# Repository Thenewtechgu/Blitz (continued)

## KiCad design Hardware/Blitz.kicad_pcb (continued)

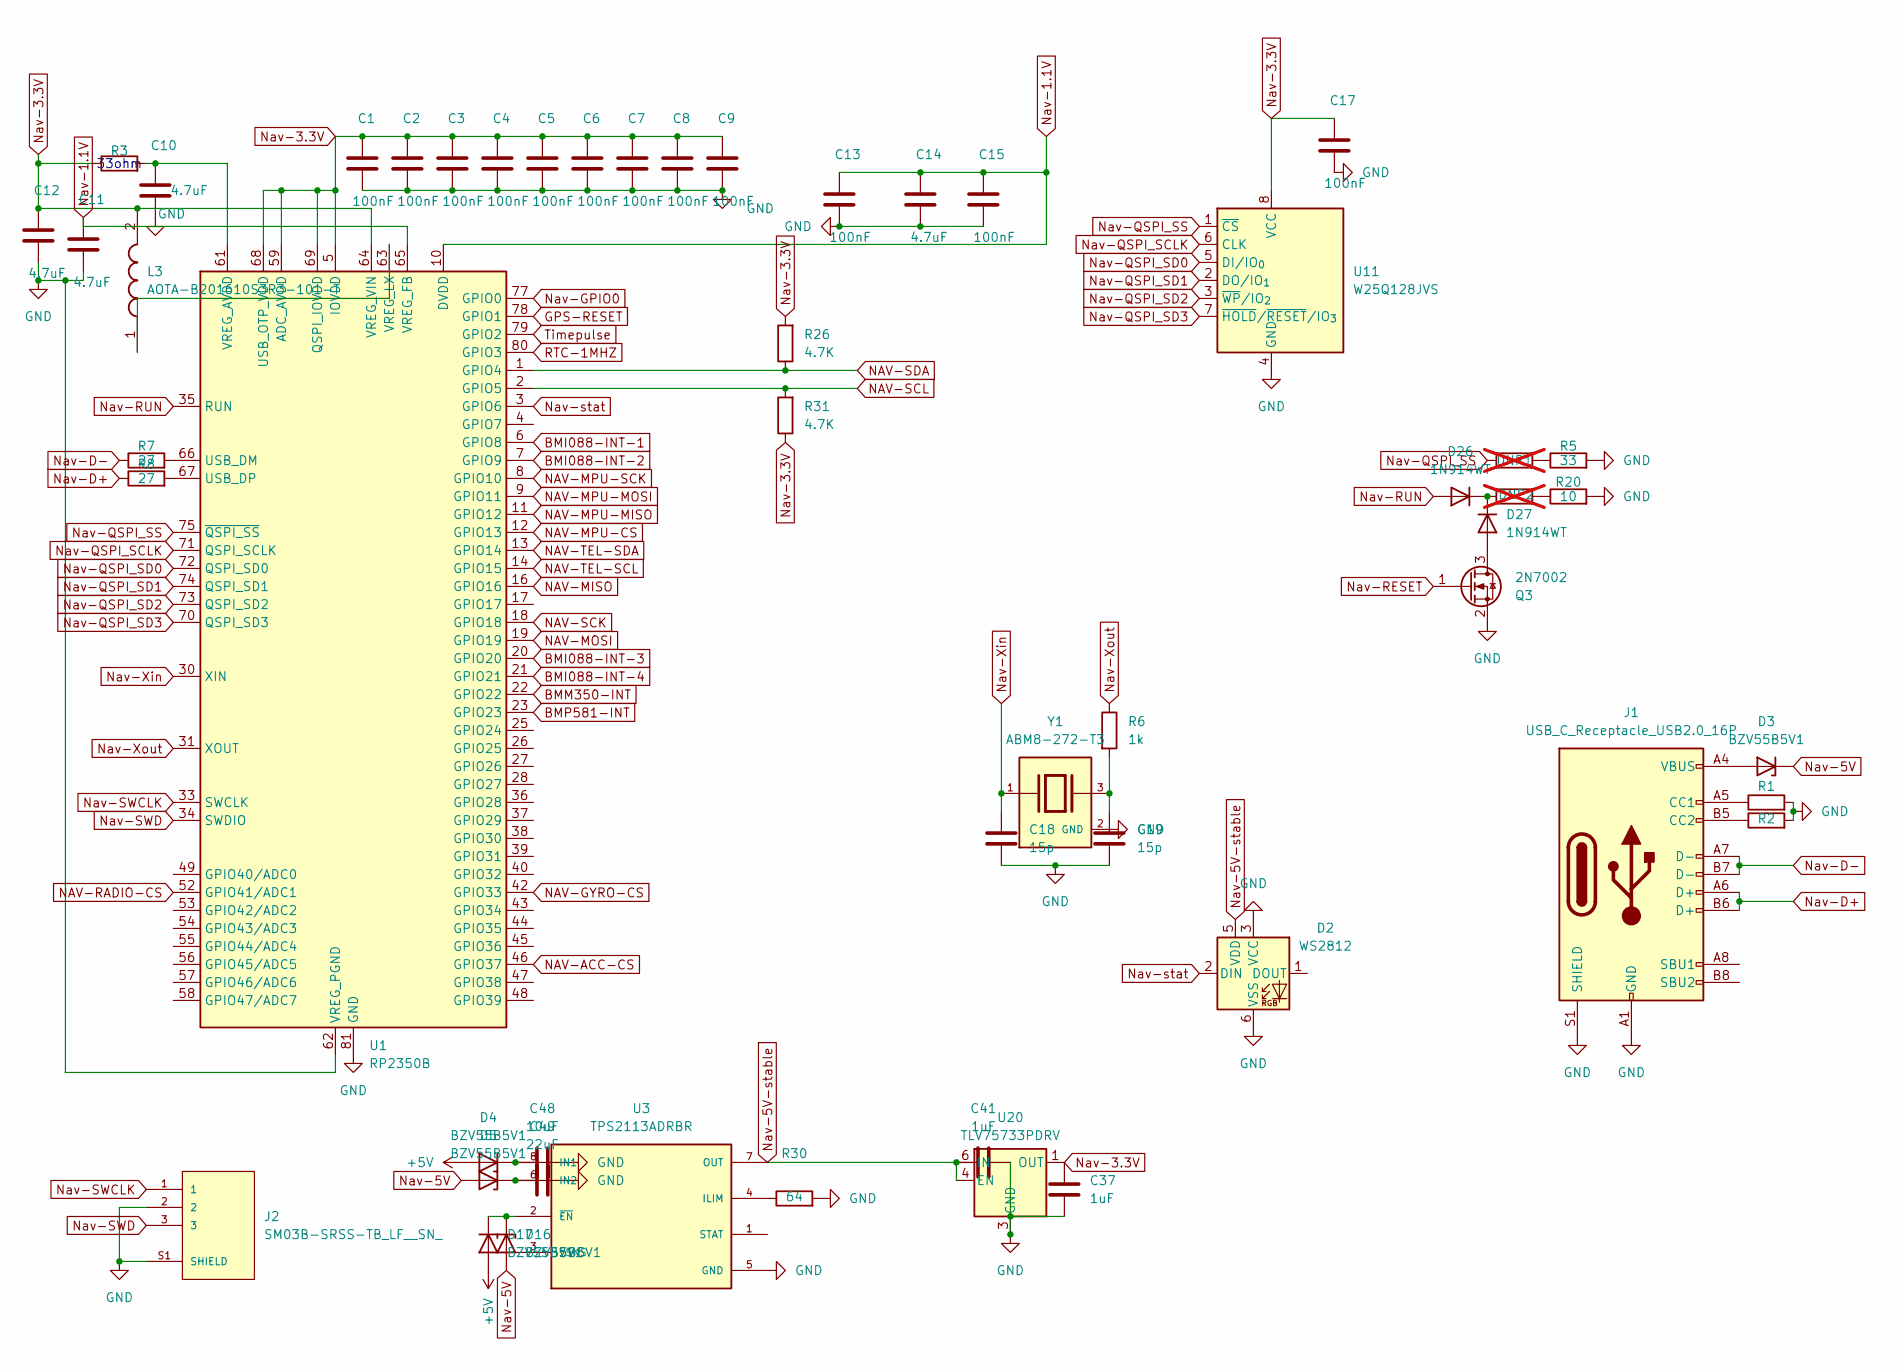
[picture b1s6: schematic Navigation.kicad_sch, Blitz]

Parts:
C1, C2, C3, C4, C5, C6, C7, C8, C9, C13, C15, C17: 100nF; C_01005_0402Metric
C10, C11, C12, C14: 4.7uF; C_01005_0402Metric
C18, C19: 15p; C_0201_0603Metric
C37, C41: 1uF; C_0402_1005Metric
C48: 10uF; C_1206_3216Metric_Pad1.33x1.80mm_HandSolder
C49: 22uF; C_1206_3216Metric_Pad1.33x1.80mm_HandSolder
D2: WS2812; LED_WS2812_PLCC6_5.0x5.0mm_P1.6mm
D3, D4, D5, D16, D17: BZV55B5V1; D_MiniMELF
D26, D27: 1N914WT; D_SOD-523
DNP1, DNP2: R; R_2010_5025Metric_Pad1.40x2.65mm_HandSolder; not fitted
J1: USB_C_Receptacle_USB2.0_16P; USB_C_Receptacle_G-Switch_GT-USB-7010ASV
J2: SM03B-SRSS-TB_LF__SN_; JST_SM03B-SRSS-TB_LF__SN_
L3: AOTA-B201610S3R3-101-T; AOTAB201610S3R3101T; Manufacturer_Part_Number AOTA-B201610S3R3-101-T; Mouser Part Number 815-AB201610S3R3101T
Q3: 2N7002; SOT-23
R1, R2: R; R_01005_0402Metric
R3: R; R_01005_0402Metric_Pad0.57x0.30mm_HandSolder
R5: 33; R_0201_0603Metric_Pad0.64x0.40mm_HandSolder
R6: 1k; R_01005_0402Metric
R7, R8: 27; R_0201_0603Metric_Pad0.64x0.40mm_HandSolder
R20: 10; R_0201_0603Metric_Pad0.64x0.40mm_HandSolder
R26, R31: 4.7K; R_0201_0603Metric
R30: 64; R_0201_0603Metric
U1: RP2350B; QFN-80-1EP_10x10mm_P0.4mm_EP3.4x3.4mm
U3: TPS2113ADRBR; SON65P300X300X100-9N; PARTREV C
U11: W25Q128JVS; SOIC-8_5.3x5.3mm_P1.27mm
U20: TLV75733PDRV; WSON-6-1EP_2x2mm_P0.65mm_EP1x1.6mm
Y1: ABM8-272-T3; XTAL_ABM8-272-T3; PARTREV 07-29-20

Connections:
+5V: D4.2 (A), D17.2 (A); also elsewhere on the board
BMI088-INT-1: U1.6 (GPIO8); also elsewhere on the board
BMI088-INT-2: U1.7 (GPIO9); also elsewhere on the board
BMI088-INT-3: U1.20 (GPIO20); also elsewhere on the board
BMI088-INT-4: U1.21 (GPIO21); also elsewhere on the board
BMM350-INT: U1.22 (GPIO22); also elsewhere on the board
BMP581-INT: U1.23 (GPIO23); also elsewhere on the board
GPS-RESET: U1.78 (GPIO1); also elsewhere on the board
NAV-ACC-CS: U1.46 (GPIO37); also elsewhere on the board
NAV-GYRO-CS: U1.42 (GPIO33); also elsewhere on the board
NAV-MISO: U1.16 (GPIO16); also elsewhere on the board
NAV-MOSI: U1.19 (GPIO19); also elsewhere on the board
NAV-MPU-CS: U1.12 (GPIO13); also elsewhere on the board
NAV-MPU-MISO: U1.11 (GPIO12); also elsewhere on the board
NAV-MPU-MOSI: U1.9 (GPIO11); also elsewhere on the board
NAV-MPU-SCK: U1.8 (GPIO10); also elsewhere on the board
NAV-RADIO-CS: U1.52 (GPIO41/ADC1)
NAV-SCK: U1.18 (GPIO18); also elsewhere on the board
NAV-SCL: R31.2, U1.2 (GPIO5)
NAV-SDA: R26.1, U1.1 (GPIO4)
NAV-TEL-SCL: U1.14 (GPIO15); also elsewhere on the board
NAV-TEL-SDA: U1.13 (GPIO14); also elsewhere on the board
Nav-1.1V: C11.1, C13.1, C14.1, C15.1, U1.10 (DVDD), U1.32 (DVDD), U1.51 (DVDD), U1.65 (VREG_FB)
Nav-3.3V: C1.1, C2.1, C3.1, C4.1, C5.1, C6.1, C7.1, C8.1, C9.1, C12.1, C17.1, C37.1, L3.2, R3.1, R26.2, R31.1, U1.5 (IOVDD), U1.15 (IOVDD), U1.24 (IOVDD), U1.29 (IOVDD), U1.41 (IOVDD), U1.50 (IOVDD), U1.59 (ADC_AVDD), U1.60 (IOVDD), U1.64 (VREG_VIN), U1.68 (USB_OTP_VDD), U1.69 (QSPI_IOVDD), U1.76 (IOVDD), U11.8 (VCC), U20.1 (OUT); also elsewhere on the board
Nav-5V: D3.1 (K), D5.2 (A), D16.2 (A)
Nav-5V-stable: C41.1, D2.5 (VDD), U3.7 (OUT), U20.4 (EN), U20.6 (IN)
Nav-D+: J1.A6 (D+), J1.B6 (D+), R8.1
Nav-D-: J1.A7 (D-), J1.B7 (D-), R7.1
Nav-GPIO0: U1.77 (GPIO0)
Nav-QSPI_SCLK: U1.71 (QSPI_SCLK), U11.6 (CLK)
Nav-QSPI_SD0: U1.72 (QSPI_SD0), U11.5 (DI/IO_{0})
Nav-QSPI_SD1: U1.74 (QSPI_SD1), U11.2 (DO/IO_{1})
Nav-QSPI_SD2: U1.73 (QSPI_SD2), U11.3 (~WP/IO_{2})
Nav-QSPI_SD3: U1.70 (QSPI_SD3), U11.7 (~HOLD/~RESET/IO_{3})
Nav-QSPI_SS: DNP1.1, U1.75 (~QSPI_SS), U11.1 (~CS)
Nav-RESET: Q3.1 (G)
Nav-RUN: D26.2 (A), U1.35 (RUN)
Nav-SWCLK: J2.1, U1.33 (SWCLK)
Nav-SWD: J2.3, U1.34 (SWDIO)
Nav-Xin: C18.1, U1.30 (XIN), Y1.1
Nav-Xout: R6.1, U1.31 (XOUT)
Nav-stat: D2.2 (DIN), U1.3 (GPIO6)
unnamed: C19.1, R6.2, Y1.3
unnamed: D3.2 (A), J1.A4 (VBUS), J1.A9 (VBUS), J1.B4 (VBUS), J1.B9 (VBUS)
unnamed: C48.1, D4.1 (K), U3.8 (IN1)
unnamed: C49.1, D5.1 (K), U3.6 (IN2)
unnamed: D16.1 (K), D17.1 (K), U3.2 (~EN)
unnamed: D26.1 (K), D27.1 (K), DNP2.1
unnamed: D27.2 (A), Q3.3 (D)
unnamed: DNP1.2, R5.1
unnamed: DNP2.2, R20.1
unnamed: J1.A5 (CC1), R1.1
unnamed: J1.B5 (CC2), R2.1
unnamed: R7.2, U1.66 (USB_DM)
unnamed: R8.2, U1.67 (USB_DP)
unnamed: C10.1, R3.2, U1.61 (VREG_AVDD)
unnamed: L3.1, U1.63 (VREG_LX)
unnamed: R30.1, U3.4 (ILIM)
RTC-1MHZ: U1.80 (GPIO3); also elsewhere on the board
Timepulse: U1.79 (GPIO2); also elsewhere on the board

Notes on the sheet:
33ohm

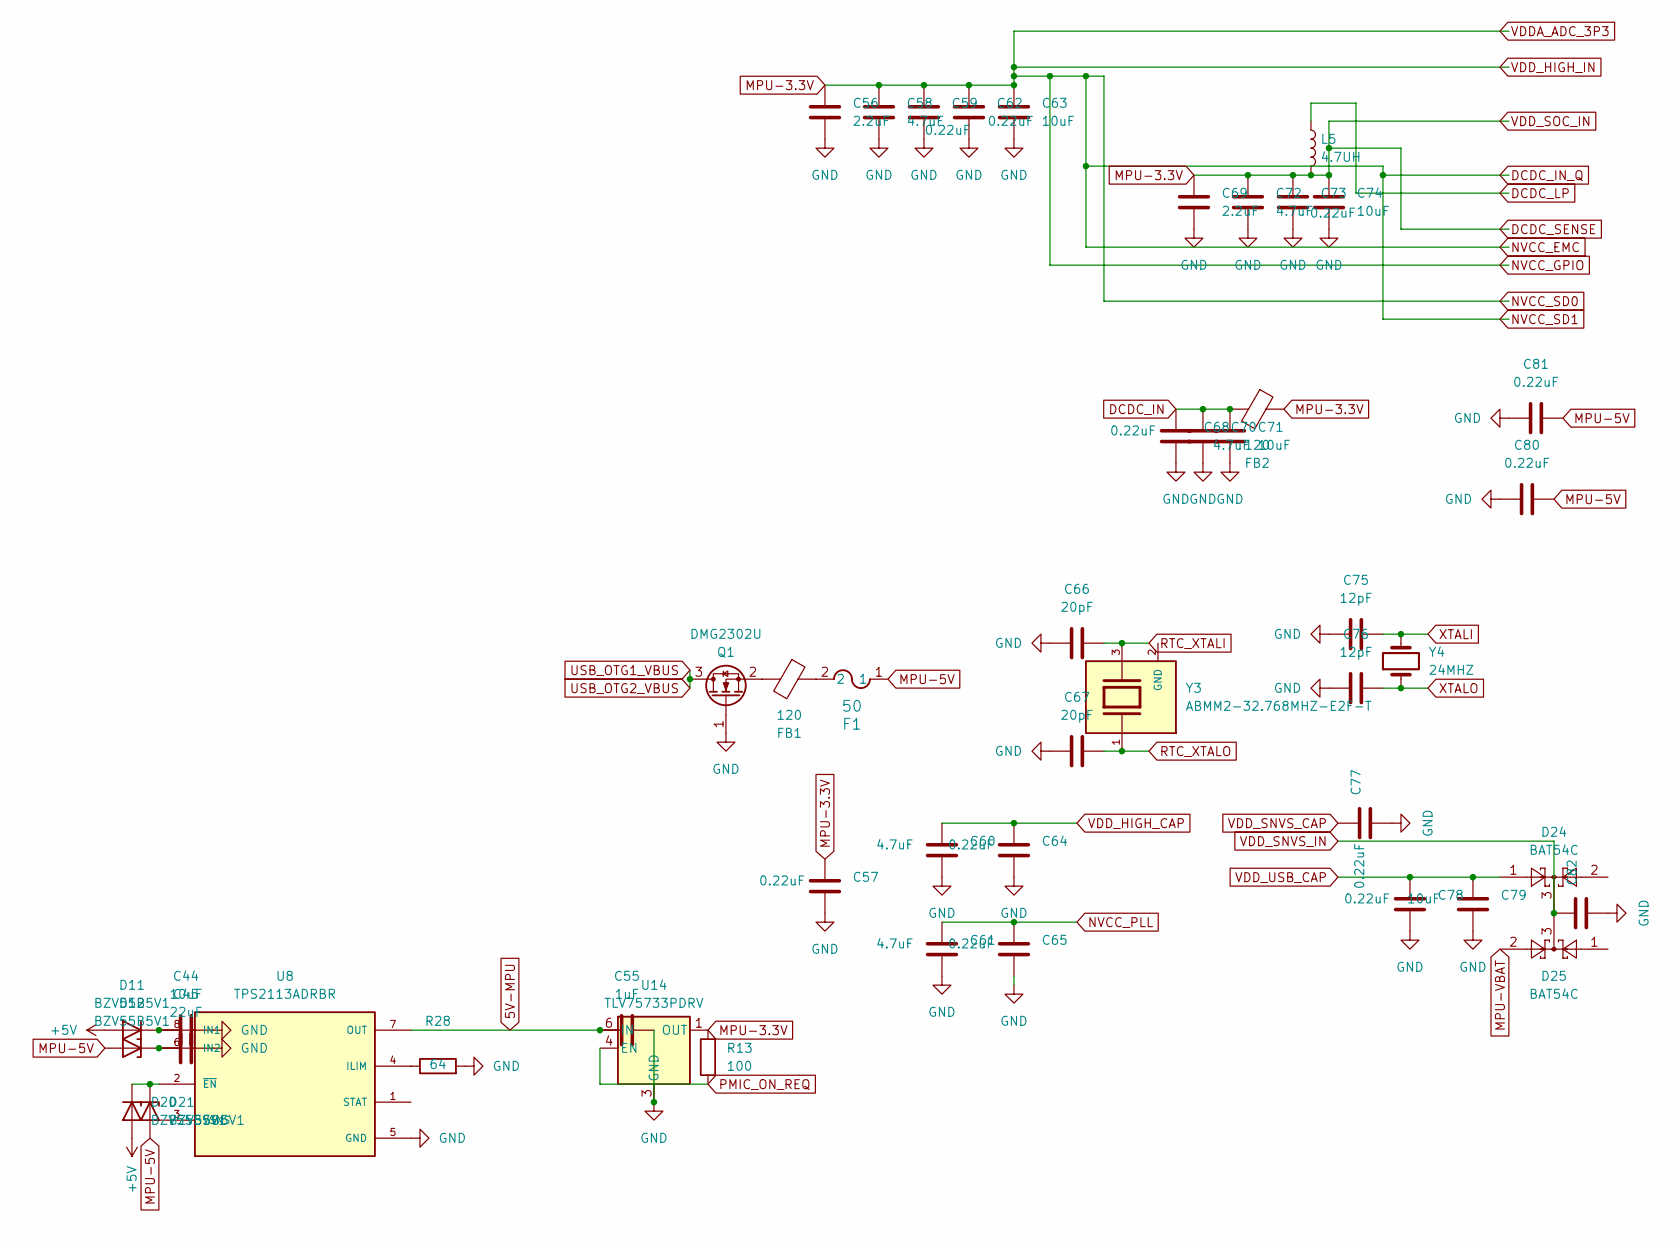
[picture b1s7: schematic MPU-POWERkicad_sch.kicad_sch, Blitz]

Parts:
C44: 10uF; C_1206_3216Metric_Pad1.33x1.80mm_HandSolder
C45: 22uF; C_1206_3216Metric_Pad1.33x1.80mm_HandSolder
C55: 1uF; C_1206_3216Metric_Pad1.33x1.80mm_HandSolder
C56, C69: 2.2uF; C_0201_0603Metric
C57, C59, C62, C64, C65, C68, C73, C77, C78, C80, C81: 0.22uF; C_0201_0603Metric
C58, C60, C61, C70, C72: 4.7uF; C_0201_0603Metric
C63, C71, C74, C79: 10uF; C_0201_0603Metric
C66, C67: 20pF; C_0201_0603Metric
C75, C76: 12pF; C_0201_0603Metric
C82: C_0201_0603Metric
D11, D12, D20, D21: BZV55B5V1; D_MiniMELF
D24, D25: BAT54C; SOT-23
F1: 50; FUSE_PTS1206_EAT
FB1, FB2: 120; L_0402_1005Metric
L5: 4.7UH; L_0201_0603Metric_Pad0.64x0.40mm_HandSolder
Q1: DMG2302U; SOT-23
R13: 100; R_0201_0603Metric
R28: 64; R_0201_0603Metric
U8: TPS2113ADRBR; SON65P300X300X100-9N; PARTREV C
U14: TLV75733PDRV; WSON-6-1EP_2x2mm_P0.65mm_EP1x1.6mm
Y3: ABMM2-32.768MHZ-E2F-T; XTAL_ABMM2-32.768MHZ-E2F-T; PARTREV 01.18.13
Y4: 24MHZ; Crystal_SMD_Abracon_ABM3-2Pin_5.0x3.2mm

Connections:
5V-MPU: C55.1, U8.7 (OUT), U14.6 (IN); also elsewhere on the board
+5V: D11.2 (A), D20.2 (A); also elsewhere on the board
DCDC_IN: C68.1, C70.1, C71.1, FB2.2; also elsewhere on the board
DCDC_IN_Q: C56.1, C57.1, C58.1, C59.1, C62.1, C63.1, C69.1, C72.1, C73.1, C74.1, FB2.1, L5.2, R13.2, U14.1 (OUT); also elsewhere on the board
DCDC_LP: L5.1; also elsewhere on the board
MPU-5V: C80.2, C81.2, D12.2 (A), D21.2 (A), F1.1; also elsewhere on the board
MPU-VBAT: D25.2
NVCC_PLL: C61.1, C65.1; also elsewhere on the board
unnamed: C44.1, D11.1 (K), U8.8 (IN1)
unnamed: C45.1, D12.1 (K), U8.6 (IN2)
unnamed: D20.1 (K), D21.1 (K), U8.2 (~EN)
unnamed: F1.2, FB1.1
unnamed: FB1.2, Q1.2 (S)
unnamed: R28.1, U8.4 (ILIM)
PMIC_ON_REQ: R13.1, U14.4 (EN); also elsewhere on the board
RTC_XTALI: C66.2, Y3.3; also elsewhere on the board
RTC_XTALO: C67.2, Y3.1; also elsewhere on the board
USB_OTG1_VBUS: Q1.3 (D); also elsewhere on the board
VDD_HIGH_CAP: C60.1, C64.1; also elsewhere on the board
VDD_SNVS_CAP: C77.1; also elsewhere on the board
VDD_SNVS_IN: C82.1, D24.3, D25.3; also elsewhere on the board
VDD_USB_CAP: C78.1, C79.1, D24.1; also elsewhere on the board
XTALI: C75.2, Y4.2; also elsewhere on the board
XTALO: C76.2, Y4.1; also elsewhere on the board

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
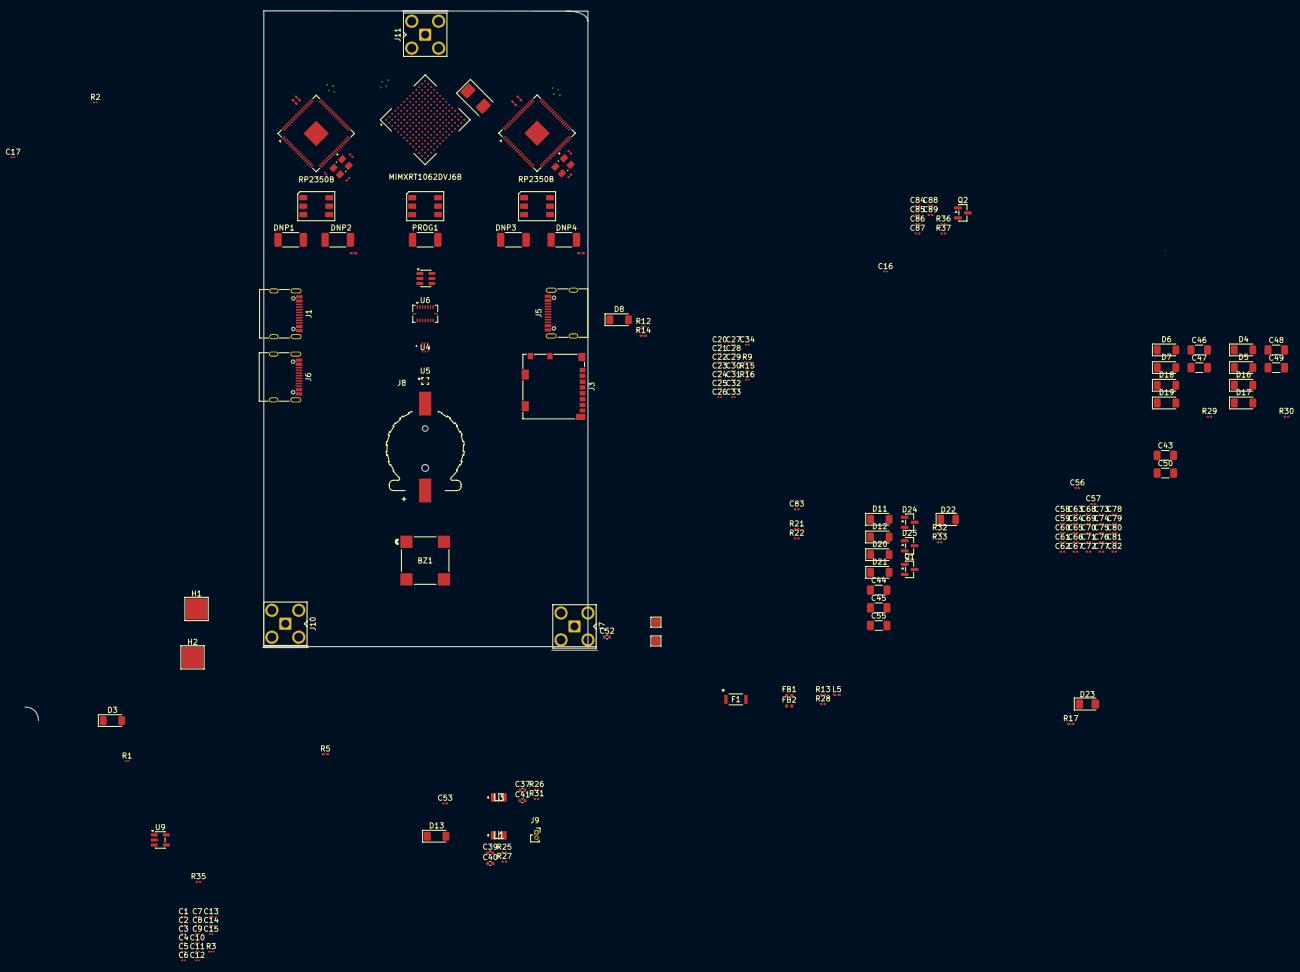
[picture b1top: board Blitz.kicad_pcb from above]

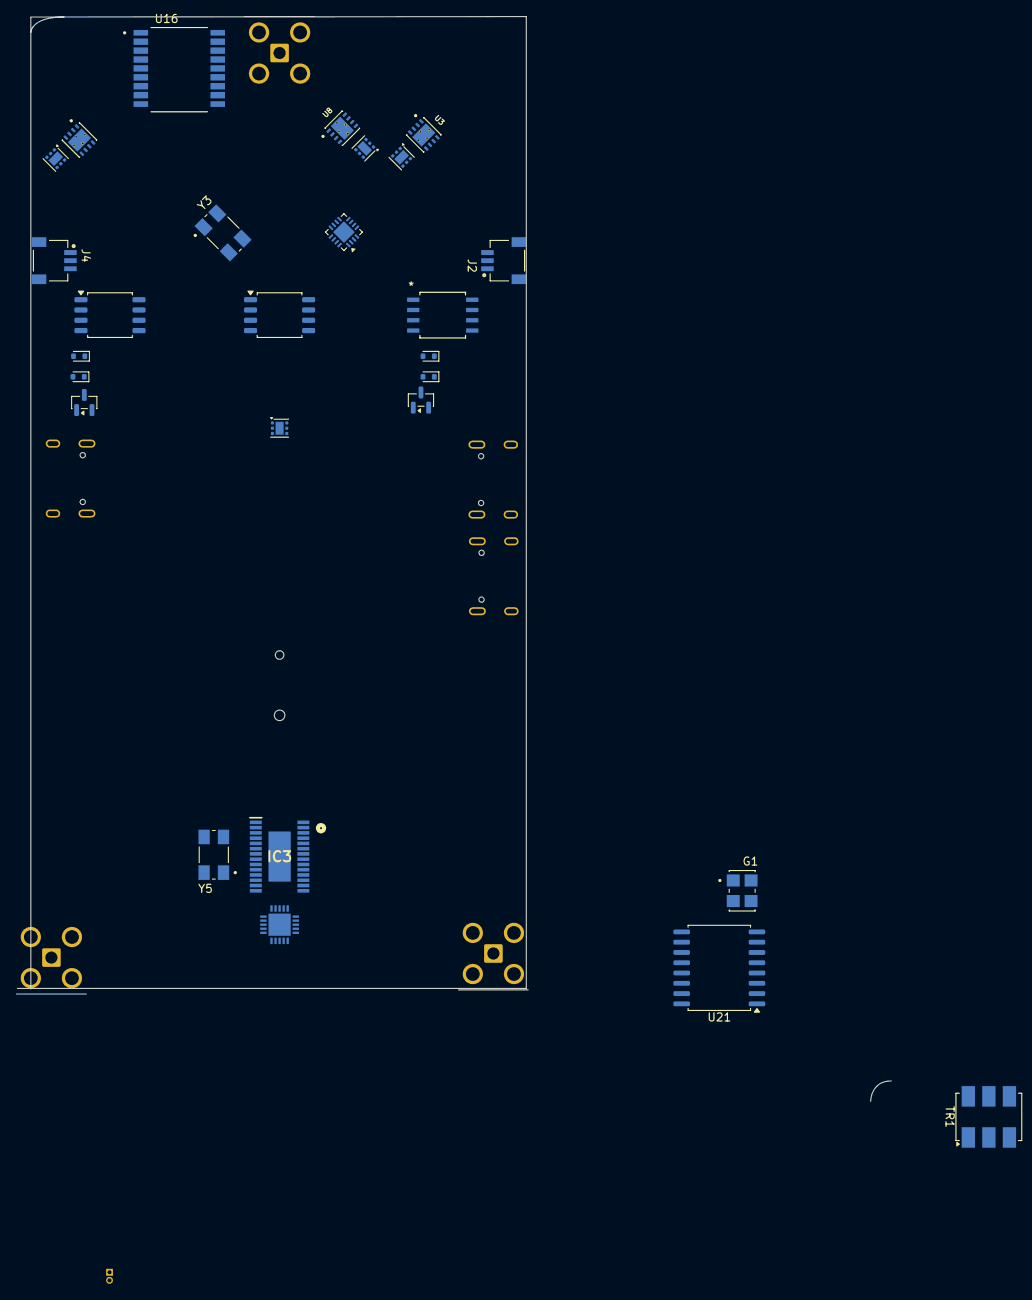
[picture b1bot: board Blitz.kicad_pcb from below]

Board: 4 copper layers, 204 parts (27 on the bottom side), 181 nets.

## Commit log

2026-02-11 datasheets
2026-02-14 Changed to Kicad
2026-02-19 Update flight controller microcontroller model in README
2026-02-19 19-feb update
2026-02-27 27 feb update
2026-03-12 12-March update
2026-03-25 test gpg
2026-03-26 test gpg again
